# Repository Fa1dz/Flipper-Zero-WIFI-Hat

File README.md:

# Flipper-Zero-WIFI-Hat
Designing a wifi hat for the flipper zero from scratch using the ESP-32 and a custom PCB. The device was designed in KiCad.

# Bill of Materials (BOM)

This BOM contains all components required for the build, including electronics, PCB fabrication, shipping estimates, and the Flipper Zero used for development/testing.

Prices are based on the supplied supplier quotes.

---

# Electronic Components

| Qty | Manufacturer | Part Number | Description | Unit Price (NOK) | Total (NOK) | Link |
| --: | ------------ | ----------- | ----------- | ---------------: | ----------: | ---- |
| 2 | Kamaya | RMC1/10K5101DTP | Thick Film Resistors - SMD 0805, 5.10 kΩ, 0.5%, Lead Free | 1.82 | 3.64 | https://no.mouser.com/en/ProductDetail/Kamaya/RMC1-10K5101DTP?qs=GedFDFLaBXG1LvR8QK0EcA%3D%3D |
| 10 | Bourns | CR2512AJW-103ELF | Thick Film Resistors - SMD 2512, 10 kΩ, 5%, 1 W | 1.08 | 10.80 | https://no.mouser.com/en/ProductDetail/Bourns/CR2512AJW-103ELF?qs=GedFDFLaBXEqggePGBQmuQ%3D%3D |
| 1 | Same Sky | UJ20-C-H-G-MSMT-4B-P16-TR | USB Connector, Type-C 2.0, Horizontal SMT, 16 Pin | 4.51 | 4.51 | https://no.mouser.com/en/ProductDetail/Same-Sky/UJ20-C-H-G-MSMT-4B-P16-TR?qs=6avfeC6zeS47Lo0obtd7QQ%3D%3D |
| 2 | Same Sky | TS04-66-65-BK-260-SMT | Tactile Switch, 6 × 6 mm, 6.5 mm Actuator, 260 gf | 1.73 | 3.46 | https://no.mouser.com/en/ProductDetail/Same-Sky/TS04-66-65-BK-260-SMT?qs=A6eO%252BMLsxmTvOTHTIBabhQ%3D%3D |
| 5 | Murata | GRM155D70G106ME18D | MLCC SMD 0402, 10 µF, 4 V, X7T, ±20% | 3.94 | 19.70 | https://no.mouser.com/en/ProductDetail/Murata/GRM155D70G106ME18D?qs=doiCPypUmgEf2sthzNH4lA%3D%3D |
| 1 | Microchip | MCP1827S-3302E/EBVAO | LDO Voltage Regulator, 3.3 V, 1.5 A | 17.74 | 17.74 | https://no.mouser.com/en/ProductDetail/Microchip/MCP1827S-3302E-EBVAO?qs=W%2FMpXkg%252BdQ5AjGztZ%252B4L5g%3D%3D |
| 1 | onsemi | 2N7002WT1G | Small Signal N-Channel MOSFET | 1.92 | 1.92 | https://no.mouser.com/en/ProductDetail/onsemi/2N7002WT1G?qs=Jh7l0IbPjidRgzyVQt6Xnw%3D%3D |
| 1 | Same Sky | CPT-1775-3TH | Board Mount Buzzer, 3 V, 75 dB, Through Hole | 10.85 | 10.85 | https://no.mouser.com/en/ProductDetail/Same-Sky/CPT-1775-3TH?qs=yc9RBI4tIAK9HFcgM%252BStOQ%3D%3D |
| 1 | Espressif | ESP32-S3-WROOM-1-N16R8 | ESP32-S3 Module, 16 MB Flash, 8 MB PSRAM, PCB Antenna | 64.73 | 64.73 | https://no.mouser.com/en/ProductDetail/Espressif/ESP32-S3-WROOM-1-N16R8?qs=Li%252BoUPsLEnvQc9gW6AMhZg%3D%3D |
| 1 | Espressif | ESP32-S3-WROOM-1U-N8 | ESP32-S3 Module, 8 MB Flash, IPEX Antenna Connector | 54.35 | 54.35 | https://no.mouser.com/en/ProductDetail/Espressif/ESP32-S3-WROOM-1U-N8?qs=Li%252BoUPsLEntthfxdhgRI1w%3D%3D |
| 1 | Taoglas | GW17.07.0250E | IPEX Terminal Antenna | 80.13 | 80.13 | https://no.mouser.com/en/ProductDetail/Taoglas/GW17.07.0250E?qs=AL7xPqYNrmTPXhCuHzQycg%3D%3D |
| 1 | Würth Elektronik | 693072010801 | MicroSD Card Connector, 8 Pin Hinge | 32.70 | 32.70 | https://no.mouser.com/en/ProductDetail/Wurth-Elektronik/693072010801?qs=7gQLVZk5cPmw4uU1mAcUFg%3D%3D |

## Electronics Subtotal

**303.53 NOK (~$31.57 USD)**

---

# PCB Manufacturing

| Qty | Item | Cost (NOK) | Link |
| --: | ---- | ---------: | ---- |
| 1 | PCB + SMT stencil including shipping | 250.00 | JLCPCB |

## PCB Subtotal

**250.00 NOK (~$26 USD)**

---

# Additional Hardware

| Qty | Item | Cost (NOK) | Link |
| --: | ---- | ---------: | ---- |
| 1 | Flipper Zero | 2656.00 | https://www.joom.com/en/products/62f661838ed09b01ebd4e0e2 |

## Hardware Subtotal

**2656.00 NOK (~$276.22 USD)**

---

# Shipping

| Item | Cost (NOK) |
| ---- | ---------: |
| Mouser shipping and tax estimate | 459.61 |

## Shipping Subtotal

**459.61 NOK (~$47.80 USD)**

---

# Final Cost Summary

| Category | NOK | USD Approx. |
| -------- | --: | ----------: |
| Electronic components | 303.53 | $31.57 |
| PCB + SMT stencil including shipping | 250.00 | $26.00 |
| Mouser shipping/tax | 459.61 | $47.80 |
| Flipper Zero | 2656.00 | $276.22 |

---

# Total Project Cost

## Complete Build

**3669.14 NOK**

**≈ $381 USD**

Budget estimate: **~$400 USD**

---

# Notes

- The BOM includes both ESP32-S3-WROOM modules:
  - ESP32-S3-WROOM-1-N16R8 (PCB antenna)
  - ESP32-S3-WROOM-1U-N8 (IPEX antenna connector)

- The Taoglas GW17.07.0250E antenna is required for the WROOM-1U module.

- Solder paste and hot plate equipment have been removed from the BOM.

- AliExpress items and shipping estimates have been removed.

- PCB cost updated to include PCB + SMT stencil + shipping.

- Prices are based on supplied order data and may change with exchange rates.

# Notes

- The BOM includes both ESP32-S3-WROOM modules:
  - ESP32-S3-WROOM-1-N16R8 (PCB antenna)
  - ESP32-S3-WROOM-1U-N8 (IPEX antenna connector)

- The Taoglas GW17.07.0250E antenna is required for the WROOM-1U module.

- Solder paste and hot plate equipment have been removed from the BOM.

- AliExpress items and shipping estimates have been removed.

- Prices are based on supplied quotes and may change with exchange rates.

# Notes

- The BOM includes both ESP32-S3-WROOM modules from the original order:
  - ESP32-S3-WROOM-1-N16R8 (PCB antenna)
  - ESP32-S3-WROOM-1U-N8 (IPEX antenna connector)
- The Taoglas GW17.07.0250E antenna is required for the WROOM-1U module.
- Solder paste and hot plate equipment have been removed from the BOM.
- AliExpress shipping estimate has been removed.
- Prices are based on the supplied order data and may change with exchange rates.

## Notes

- ESP32-S3-WROOM-1-N16R8 and ESP32-S3-WROOM-1U-N8 are both included from the original order list.
- The Taoglas GW17.07.0250E antenna is used with the ESP32-S3-WROOM-1U-N8 module.
- Assembly tools and solder paste have been removed from this BOM.
- Prices are based on the supplied quotes and may change with exchange rates and supplier pricing.
## Notes

- The BOM includes both ESP32-S3-WROOM variants as listed in the order:
  - ESP32-S3-WROOM-1-N16R8 (PCB antenna)
  - ESP32-S3-WROOM-1U-N8 (IPEX antenna)
- The Taoglas GW17.07.0250E antenna is required for the WROOM-1U module.
- Prices are based on the supplied Mouser/JLCPCB/AliExpress/Joom estimates.
- USD conversions are approximate and will vary with exchange rates.

*Approx 255 dollars to be safe*

Features:
USB-C for flashing the ESP-32-S3-WROOM-1 module
ISTP port for antennas
Bluetooth Low Energy compatibiltiy
WIFI 2.4ghz compatability
Fully designed for Flipper Zero pins
Is compatible with Flipper Zero wifi marauder
MicroSD compatible for storage of large data packets to prevent cluttering of the UART communication

Here are some pictures of the design:

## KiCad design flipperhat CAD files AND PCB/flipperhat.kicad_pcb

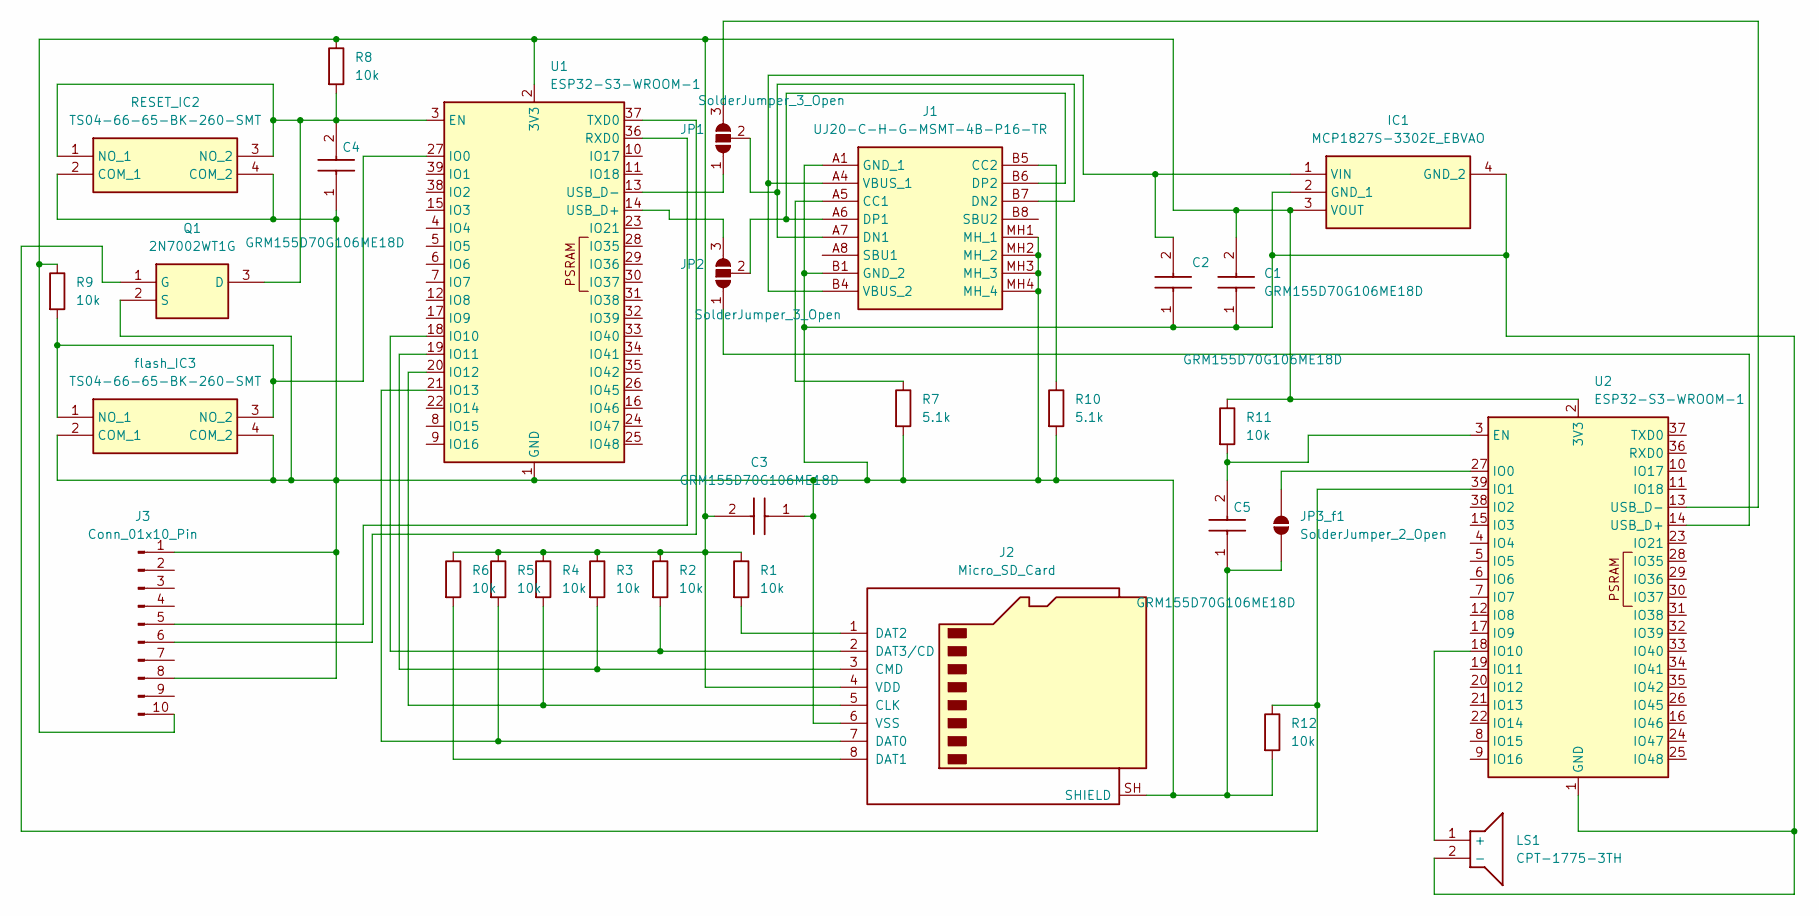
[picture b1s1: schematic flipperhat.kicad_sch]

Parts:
C1, C2, C3, C4, C5: GRM155D70G106ME18D; CAPC1005X70N; Manufacturer_Part_Number GRM155D70G106ME18D
IC1: MCP1827S-3302E_EBVAO; MCP1827S3302EEBVAO; Manufacturer_Part_Number MCP1827S-3302E/EBVAO
J1: UJ20-C-H-G-MSMT-4B-P16-TR; UJ20CHGMSMT4BP16TR; Manufacturer_Part_Number UJ20-C-H-G-MSMT-4B-P16-TR
J2: Micro_SD_Card; microSD_HC_Wuerth_693072010801
J3: Conn_01x10_Pin; PinHeader_1x10_P2.54mm_Vertical
JP1, JP2: SolderJumper_3_Open; SolderJumper-3_P1.3mm_Open_RoundedPad1.0x1.5mm
JP3_f1: SolderJumper_2_Open; SolderJumper-2_P1.3mm_Open_RoundedPad1.0x1.5mm
LS1: CPT-1775-3TH; CPT17753TH; Manufacturer_Part_Number CPT-1775-3TH
Q1: 2N7002WT1G; SOT65P220X100-3N; Mouser Part Number 863-2N7002WT1G
R1, R2, R3, R4, R5, R6, R8, R9, R11, R12: 10k; R_2512_6332Metric_Pad1.40x3.35mm_HandSolder
R7, R10: 5.1k; R_0805_2012Metric_Pad1.20x1.40mm_HandSolder
RESET_IC2: TS04-66-65-BK-260-SMT; TS046665BK260SMT; Mouser Part Number 179-TS046665BK260SMT
U1, U2: ESP32-S3-WROOM-1
flash_IC3: TS04-66-65-BK-260-SMT; TS046665BK260SMT; Mouser Part Number 179-TS046665BK260SMT

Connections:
unnamed: C1.1, C2.1, C3.1, C4.1, C5.1, IC1.2 (GND_1), IC1.4 (GND_2), J1.A1 (GND_1), J1.B1 (GND_2), J1.MH1 (MH_1), J1.MH2 (MH_2), J1.MH3 (MH_3), J1.MH4 (MH_4), J2.6 (VSS), J2.SH (SHIELD), J3.1, J3.8, JP3_f1.1 (A), LS1.2 (-), Q1.2 (S), R7.2, R10.2, R12.2, RESET_IC2.2 (COM_1), RESET_IC2.4 (COM_2), U1.1 (GND), U1.40 (GND), U1.41 (GND), U2.1 (GND), U2.40 (GND), U2.41 (GND), flash_IC3.2 (COM_1), flash_IC3.4 (COM_2)
unnamed: C2.2, IC1.1 (VIN), J1.A4 (VBUS_1), J1.B4 (VBUS_2)
unnamed: C1.2, C3.2, IC1.3 (VOUT), J2.4 (VDD), J3.10, R1.1, R2.1, R3.1, R4.1, R5.1, R6.1, R8.1, R9.1, R11.1, U1.2 (3V3), U2.2 (3V3)
unnamed: J1.A5 (CC1), R7.1
unnamed: J1.B5 (CC2), R10.1
unnamed: J1.A7 (DN1), J1.B7 (DN2), JP1.2 (C)
unnamed: J1.A6 (DP1), J1.B6 (DP2), JP2.2 (C)
unnamed: J2.5 (CLK), R4.2, U1.20 (IO12)
unnamed: J2.3 (CMD), R3.2, U1.19 (IO11)
unnamed: J2.7 (DAT0), R5.2, U1.21 (IO13)
unnamed: J2.8 (DAT1), R6.2
unnamed: J2.1 (DAT2), R1.2
unnamed: J2.2 (DAT3/CD), R2.2, U1.18 (IO10)
unnamed: J3.5, U1.36 (RXD0)
unnamed: J3.6, U1.37 (TXD0)
unnamed: JP1.1 (A), U1.13 (USB_D-)
unnamed: JP1.3 (B), U2.13 (USB_D-)
unnamed: JP2.1 (A), U2.14 (USB_D+)
unnamed: JP2.3 (B), U1.14 (USB_D+)
unnamed: JP3_f1.2 (B), U2.27 (IO0)
unnamed: LS1.1 (+), U2.18 (IO10)
unnamed: C4.2, Q1.3 (D), R8.2, RESET_IC2.1 (NO_1), RESET_IC2.3 (NO_2), U1.3 (EN)
unnamed: Q1.1 (G), R12.1, U2.39 (IO1)
unnamed: R9.2, U1.27 (IO0), flash_IC3.1 (NO_1), flash_IC3.3 (NO_2)
unnamed: C5.2, R11.2, U2.3 (EN)

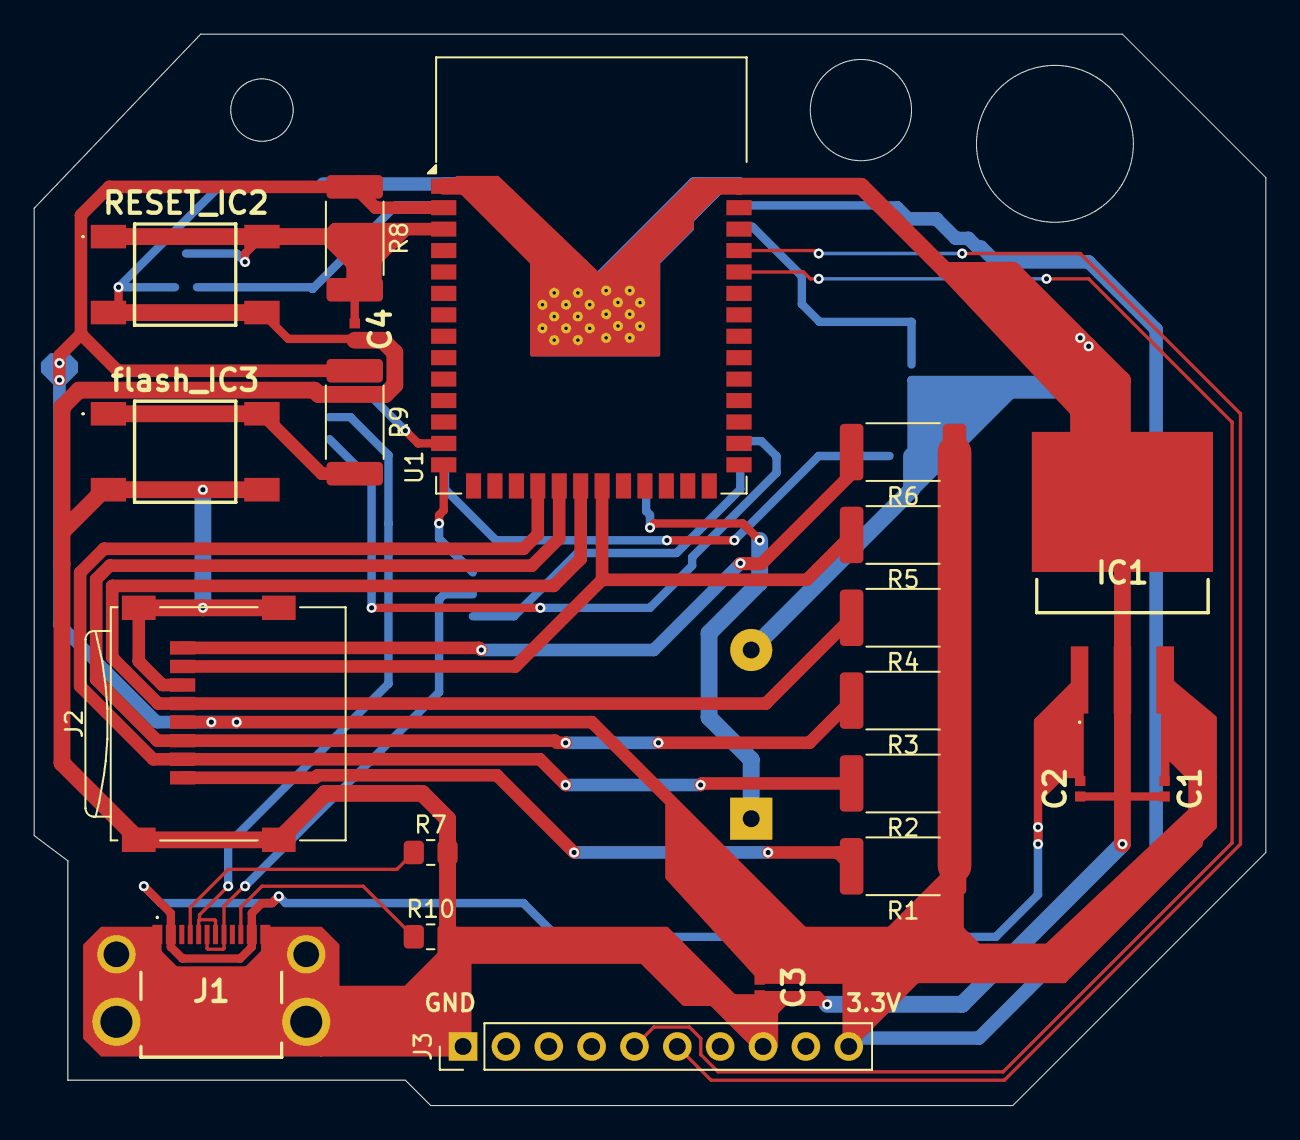
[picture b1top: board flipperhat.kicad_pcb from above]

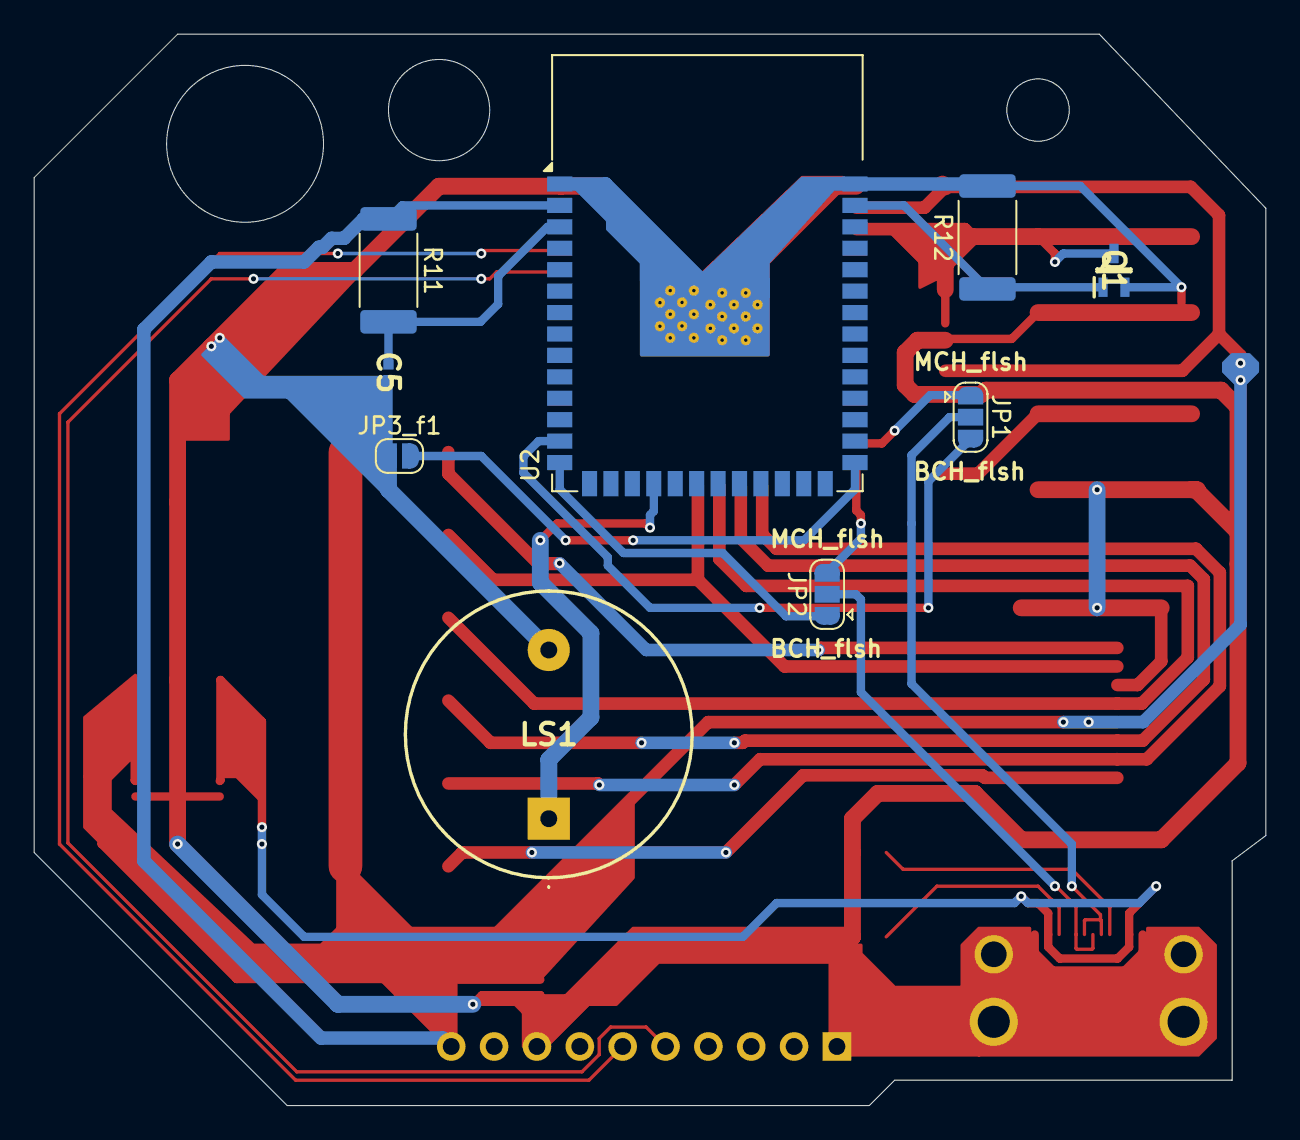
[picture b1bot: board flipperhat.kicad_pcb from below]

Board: 2 copper layers, 73.0 x 63.5 mm, 30 parts (9 on the bottom side), 25 nets.

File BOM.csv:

FLIPPER_HAT,,,,,,,,,,,,
Mouser No,Mfr. No,Manufacturer,Customer No,Description ,RoHS,Lifecycle,Order Qty.,Price (EUR),Ext.: (EUR),Country of Origin,Assembly Country of Origin,Country of Diffusion
791-RMC1/10K5101DTP,RMC1/10K5101DTP,Kamaya,,Thick Film Resistors - SMD 0805   5K10   0.5%   Lead Free,RoHS Compliant By Exemption,,2,"0,163 ?","0,33 ?",Malaysia,,
652-CR2512AJW-103ELF,CR2512AJW-103ELF,Bourns,,Thick Film Resistors - SMD ResA 2512 10k 5% 1W TC200,RoHS Compliant By Exemption,,9,"0,232 ?","2,09 ?",Taiwan,,
179-CHGMSMT4BP16TR,UJ20-C-H-G-MSMT-4B-P16-TR,Same Sky,,"USB Connectors USB Jack, Type C, 2.0, MSMT, Horizontal, Gold Flash, 16 Pin, TR",RoHS Compliant,New Product,1,"0,404 ?","0,40 ?",China,,
179-TS046665BK260SMT,TS04-66-65-BK-260-SMT,Same Sky,,"Tactile Switches 6 x 6 mm, 6.5 mm Act Height, 260 gf, Black, Surface Mount, SPST,",RoHS Compliant,,2,"0,163 ?","0,33 ?",China,,
81-GRM155D70G106ME8D,GRM155D70G106ME18D,Murata,,Multilayer Ceramic Capacitors MLCC - SMD/SMT 0402 4VDC 10uF 20% X7T,RoHS Compliant,New Product,5,"0,353 ?","1,77 ?",Japan,,
579-M827S302EEBVAO,MCP1827S-3302E/EBVAO,Microchip,,LDO Voltage Regulators 1.5A LDO Regulator,RoHS Compliant,New Product,1,"1,59 ?","1,59 ?",China,,
863-2N7002WT1G,2N7002WT1G,onsemi,,MOSFETs SMALL SIGNAL MOSFET 6.8V LO C,RoHS Compliant,,1,"0,172 ?","0,17 ?",China,China,Taiwan
179-CPT-1775-3TH,CPT-1775-3TH,Same Sky,,"Buzzers & Audio Indicators - Board Mount buzzer, 17 mm x 7.5 mm deep, P, 3 V, 75 dB, Through Hole, Audio Transducer",RoHS Compliant,New Product,1,"0,972 ?","0,97 ?",China,,
356-ESP32S3WRM1N16R8,ESP32-S3-WROOM-1-N16R8,Espressif,,"Multiprotocol Modules SMD module, ESP32-S3R8 with 3.3V, 8 MB Octal PSRAM die inside, 16 MB Quad SPI flash, PCB antenna",RoHS Compliant,,1,"5,80 ?","5,80 ?",China,,
356-ESP32S3WROOM1UN8,ESP32-S3-WROOM-1U-N8,Espressif,,"Multiprotocol Modules SMD module, ESP32-S3, 8 MB SPI flash, IPEX antenna connector",RoHS Compliant,,1,"4,87 ?","4,87 ?",China,,
960-GW.17.07.0250E,GW17.07.0250E,Taoglas,,Antennas IPEX TERMINAL ANTENNA,RoHS Compliant,,1,"11,53 ?","11,53 ?",Taiwan,,
485-5903,5903,Adafruit,,Soldering & Desoldering Stations Mini Brass Hot Plate Preheater with USB-C PD or DC - MHP50-B5,RoHS Compliant,,1,"111,75 ?","111,75 ?",China,,
910-RMA591AX10,RMA591AX10,Chip Quik,,Solder RMA Solder Paste SN63/PB37 T4 (35g Syringe),No,New At Mouser,1,"14,60 ?","14,60 ?",Canada,,
